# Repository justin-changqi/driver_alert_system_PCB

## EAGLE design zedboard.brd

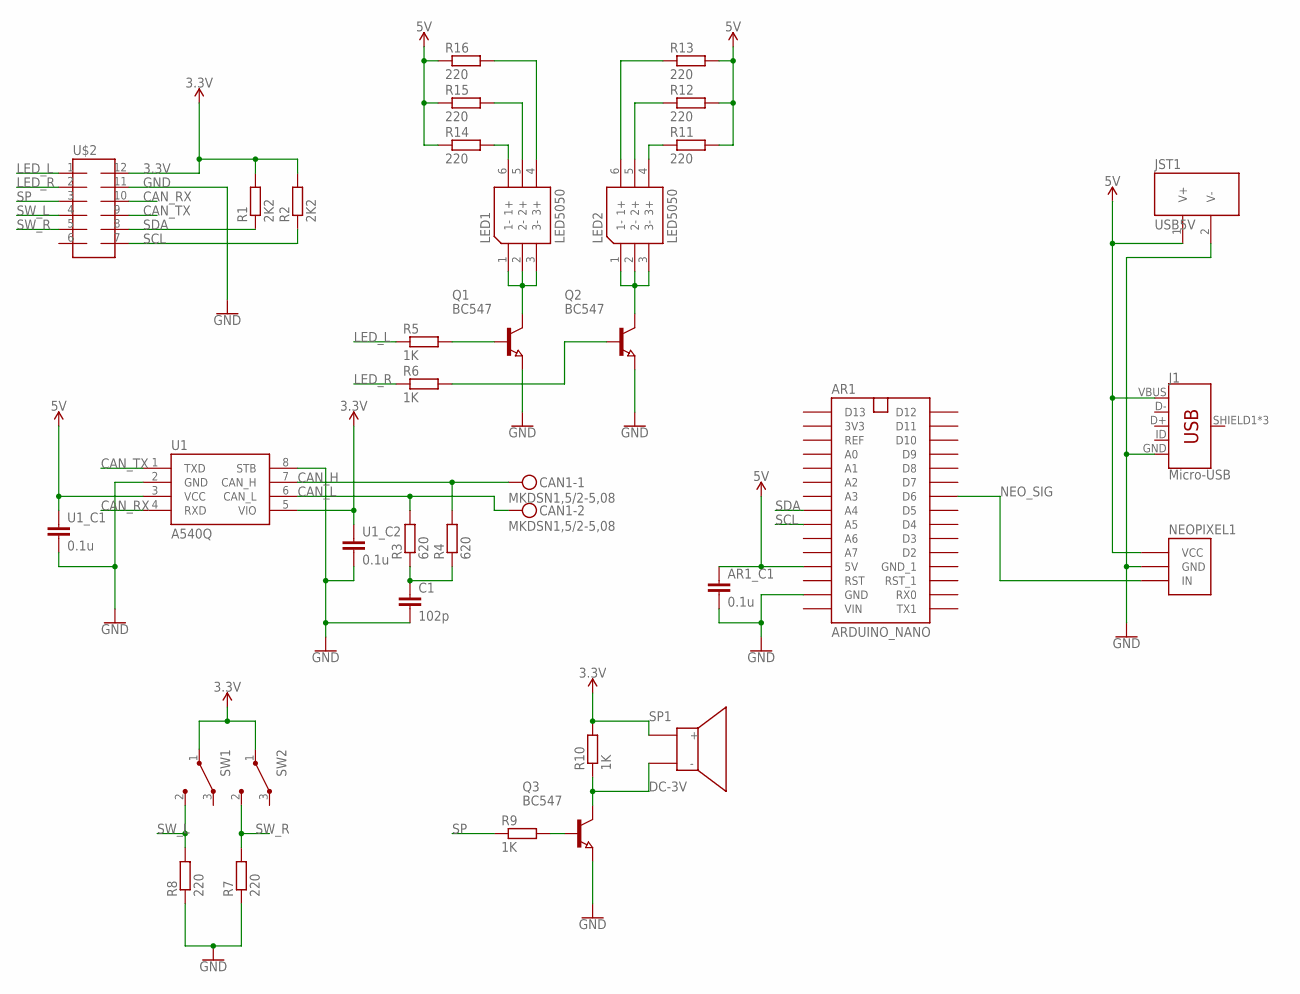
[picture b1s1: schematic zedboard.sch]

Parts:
AR1: ARDUINO_NANO
AR1_C1: 0.1u; C0805
C1: 102p; C1206
CAN1: MKDSN1,5/2-5,08
J1: Micro-USB; USB-B-MICRO-SMD_RED_PASTE
JST1: USB5V; POWER_2MM
LED1, LED2: LED5050; LED-TRICOLOR-5050
NEOPIXEL1: NEOPIXEL; NEOPIXEL_RING_16
Q1, Q2, Q3: BC547; SOT23
R1, R2: 2K2; R0805
R3, R4: 620; R1206
R5, R6, R9, R10: 1K; R1206
R7, R8, R11, R12, R13, R14, R15, R16: 220; R1206
SP1: DC-3V; SPEAKER_2MM_CON
SW1, SW2: 1A125V; MICRO_SW_1A
U1: A540Q; SOIC8
U1_C1, U1_C2: 0.1u; C0805
U$2: HEARDER_6X2; HEADER_6X2_L

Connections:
3.3V: R1.2, R2.2, R10.2, SP1.P$1 (+), SW1.1 (C), SW2.1 (C), U1.5 (VIO), U1_C2.1, U$2.12
5V: AR1.P$12 (5V), AR1_C1.1, J1.VBUS, JST1.1 (V+), NEOPIXEL1.P$1 (VCC), R11.2, R12.2, R13.2, R14.1, R15.1, R16.1, U1.3 (VCC), U1_C1.1
CAN_H: CAN1.1, R4.2, U1.7 (CAN_H)
CAN_L: CAN1.2, R3.2, U1.6 (CAN_L)
CAN_RX: U1.4 (RXD), U$2.10
CAN_TX: U1.1 (TXD), U$2.9
GND: AR1.P$14 (GND), AR1_C1.2, C1.2, J1.GND, JST1.2 (V-), NEOPIXEL1.P$2 (GND), Q1.2 (E), Q2.2 (E), Q3.2 (E), R7.1, R8.1, U1.2 (GND), U1.8 (STB), U1_C1.2, U1_C2.2, U$2.11
LED_L: R5.1, U$2.1
LED_R: R6.1, U$2.2
unnamed: C1.1, R3.1, R4.1
unnamed: Q1.1 (B), R5.2
unnamed: LED1.1 (1-), LED1.2 (2-), LED1.3 (3-), Q1.3 (C)
unnamed: LED2.1 (1-), LED2.2 (2-), LED2.3 (3-), Q2.3 (C)
unnamed: Q2.1 (B), R6.2
unnamed: Q3.3 (C), R10.1, SP1.P$2 (-)
unnamed: Q3.1 (B), R9.2
unnamed: LED1.4 (3+), R16.2
unnamed: LED1.5 (2+), R15.2
unnamed: LED1.6 (1+), R14.2
unnamed: LED2.4 (3+), R11.1
unnamed: LED2.5 (2+), R12.1
unnamed: LED2.6 (1+), R13.1
NEO_SIG: AR1.P$24 (D6), NEOPIXEL1.P$3 (IN)
SCL: AR1.P$9 (A5), R2.1, U$2.7
SDA: AR1.P$8 (A4), R1.1, U$2.8
SP: R9.1, U$2.3
SW_L: R8.2, SW1.2 (NO), U$2.4
SW_R: R7.2, SW2.2 (NO), U$2.5

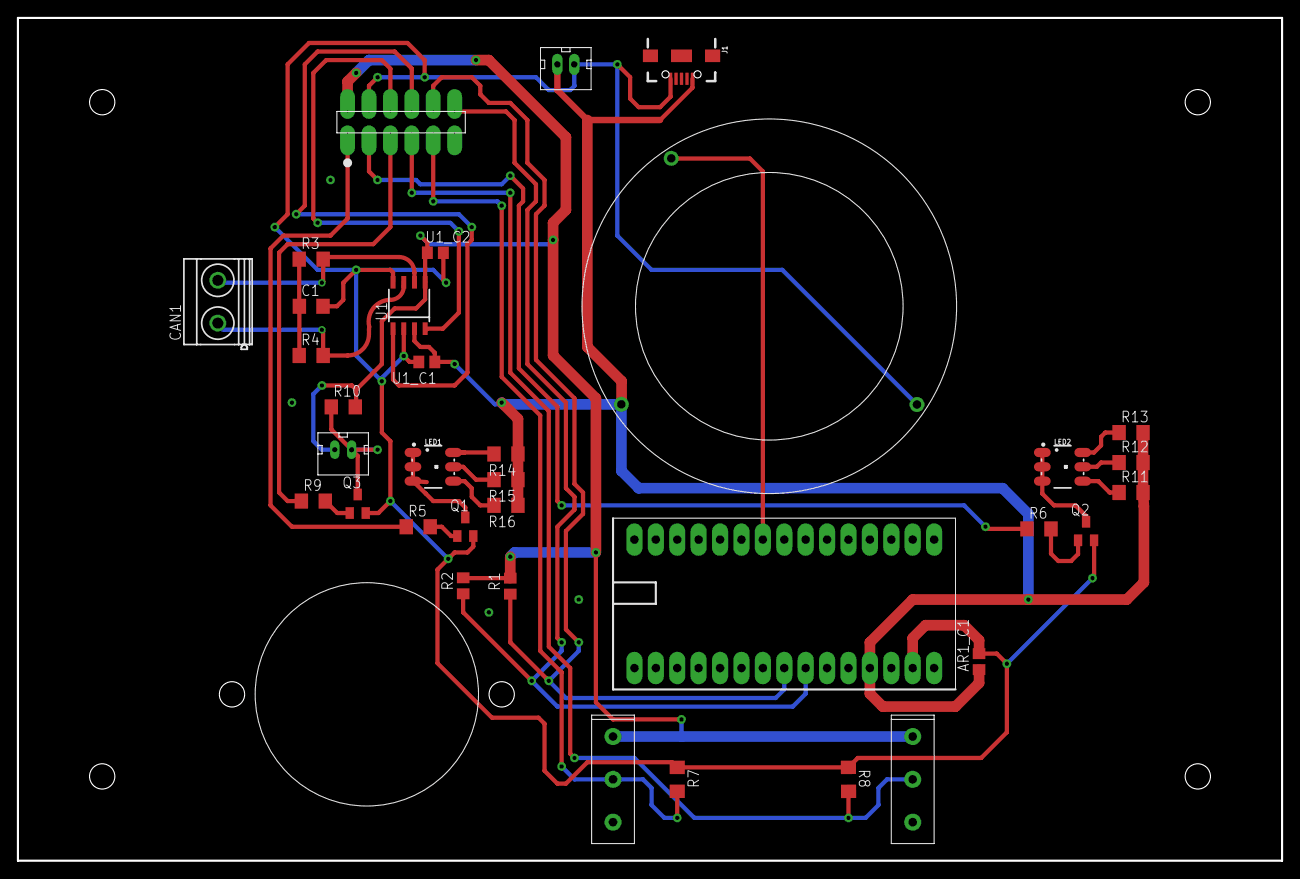
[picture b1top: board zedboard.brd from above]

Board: 2 copper layers, 150.0 x 100.0 mm, 35 parts (0 on the bottom side), 28 nets.

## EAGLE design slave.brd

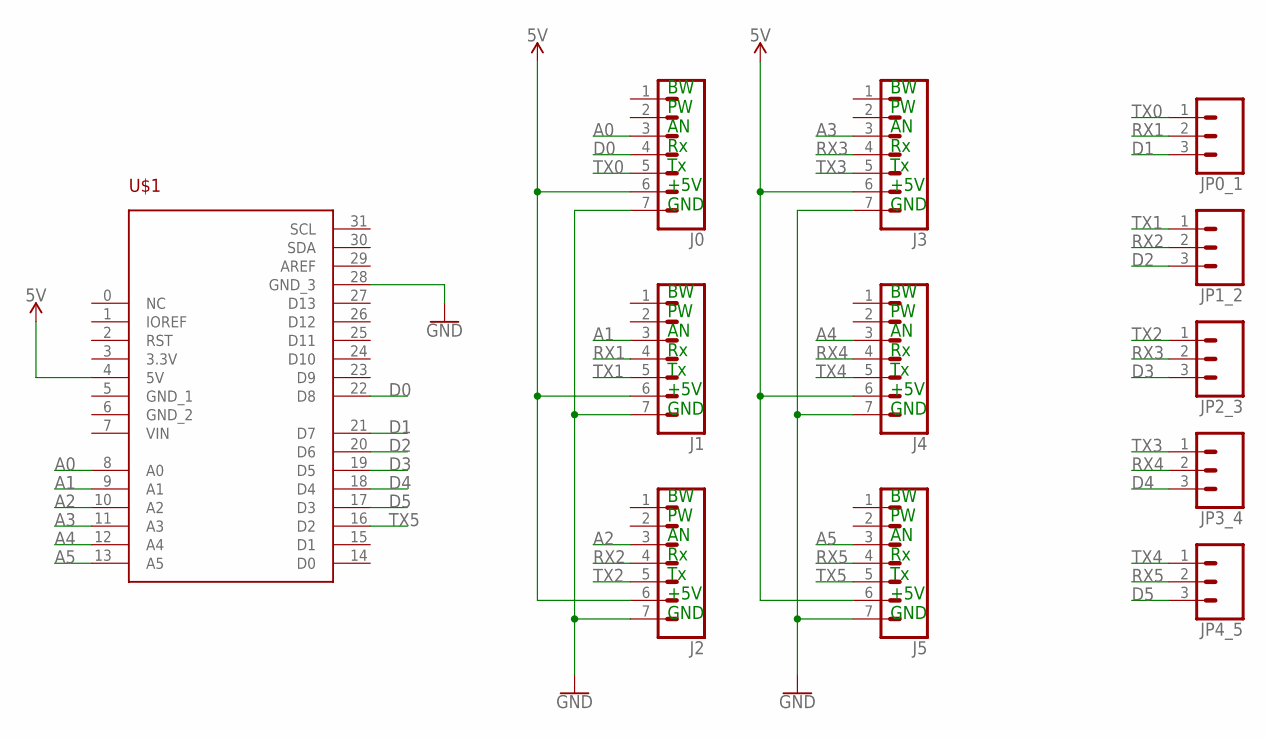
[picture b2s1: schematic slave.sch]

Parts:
J0, J1, J2, J3, J4, J5: CONN_07LONGPADS; 1X07_LONGPADS
JP0_1, JP1_2, JP2_3, JP3_4, JP4_5: CONN_03LONGPADS; 1X03_LONGPADS
U$1: ARDUINO_UNO_STACK

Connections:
3.3V: U$1.3 (3.3V)
5V: J0.6, J1.6, J2.6, J3.6, J4.6, J5.6, U$1.4 (5V)
A0: J0.3, U$1.8 (A0)
A1: J1.3, U$1.9 (A1)
A2: J2.3, U$1.10 (A2)
A3: J3.3, U$1.11 (A3)
A4: J4.3, U$1.12 (A4)
A5: J5.3, U$1.13 (A5)
D0: J0.4, U$1.22 (D8)
D1: JP0_1.3, U$1.21 (D7)
D2: JP1_2.3, U$1.20 (D6)
D3: JP2_3.3, U$1.19 (D5)
D4: JP3_4.3, U$1.18 (D4)
D5: JP4_5.3, U$1.17 (D3)
GND: J0.7, J1.7, J2.7, J3.7, J4.7, J5.7, U$1.28 (GND_3)
GND_1: U$1.5 (GND_1)
GND_2: U$1.6 (GND_2)
RX1: J1.4, JP0_1.2
RX2: J2.4, JP1_2.2
RX3: J3.4, JP2_3.2
RX4: J4.4, JP3_4.2
RX5: J5.4, JP4_5.2
TX0: J0.5, JP0_1.1
TX1: J1.5, JP1_2.1
TX2: J2.5, JP2_3.1
TX3: J3.5, JP3_4.1
TX4: J4.5, JP4_5.1
TX5: J5.5, U$1.16 (D2)
VIN: U$1.7 (VIN)

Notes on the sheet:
BW PW AN Rx Tx +5V GND

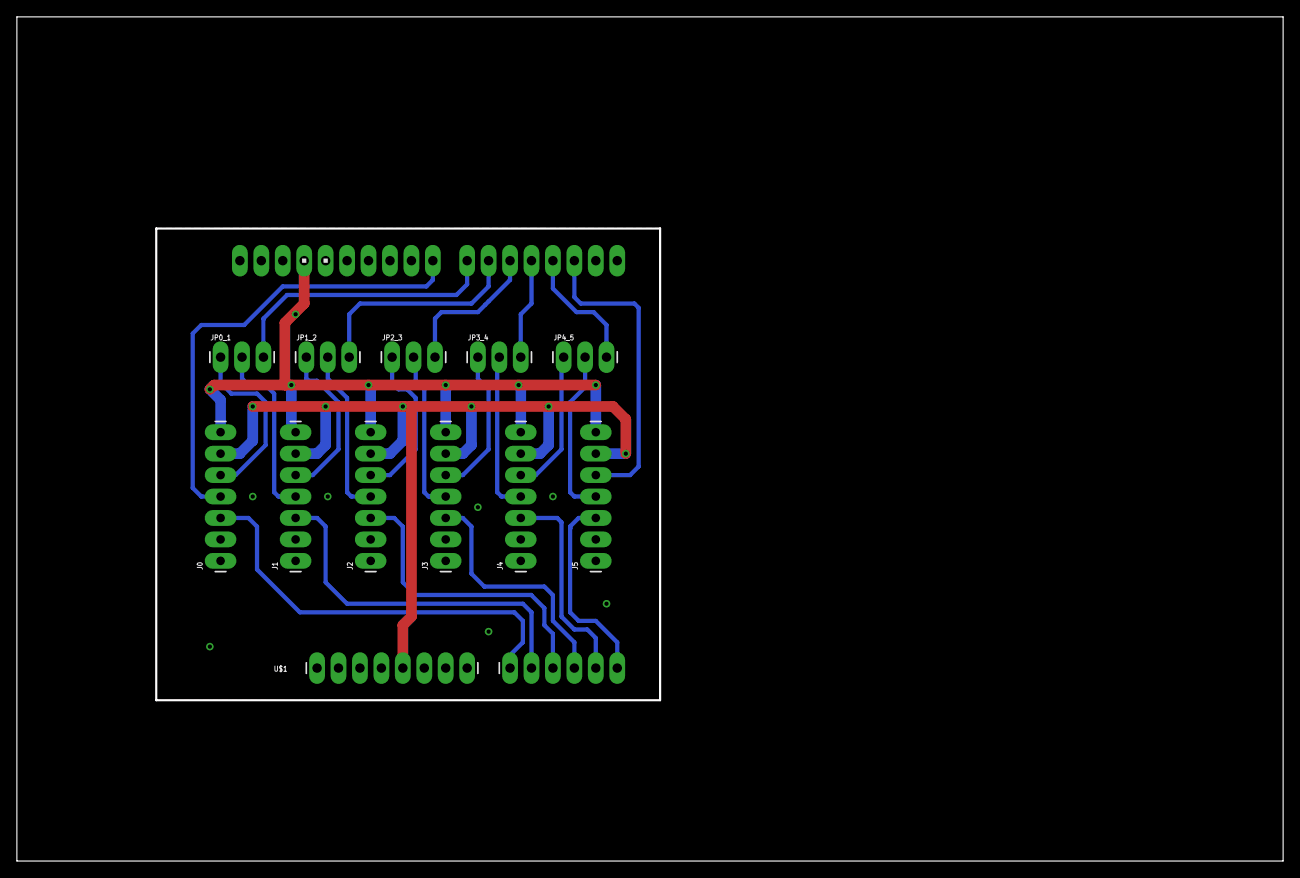
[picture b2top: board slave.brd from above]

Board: 2 copper layers, 150.0 x 100.0 mm, 12 parts (0 on the bottom side), 25 nets.

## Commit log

2018-06-13 increase size of routes
2018-06-15 Fix arduino uno pcb not fit
2018-06-15 add zedbord circuit
2018-06-16 update for CAN Bus shield
2018-06-16 finish design

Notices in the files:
parts and their libraries:
SparkFun-Connectors: Licensing: Creative Commons ShareAlike 4.0 International - https://creativecommons.org/licenses/by-sa/4.0
